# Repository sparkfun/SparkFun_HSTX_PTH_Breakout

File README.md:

SparkFun HSXT PTH Breakout
========================================

[*SparkFun HSTX PTH Breakout (BOB-28467)*](https://www.sparkfun.com/sparkfun-hstx-pth-breakout.html)

The SparkFun HSTX PTH Breakout is a simple board designed to work with the HSTX connector on the IoT RedBoard - RP2350 and the camera and display connectors on a Rasbperry Pi 5. It breaks out all 22 of the pins used on these connectors to a standard 0.1"-spaced plated through hole header. These 22-pin connectors interface with a matching flexible cable and normally connect directly to other peripherals (cameras, displays, etc.).

Intended for prototyping with the IoT RedBoard - RP2350, this board breaks out all four differential pairs on the connector along with I<sup>2</sup>C signals (data/clock) and power (3.3V & Ground). 

Repository Contents
-------------------

* **/Hardware** - Eagle design files (.brd, .sch)

Product Versions
----------------
* [BOB-28467](https://www.sparkfun.com/sparkfun-hstx-pth-breakout.html) - HSXT to PTH Breakout

License Information
-------------------

This product is _**open source**_! 

Please review the LICENSE.md file for license information. 

If you have any questions or concerns on licensing, please contact technical support on our [SparkFun forums](https://forum.sparkfun.com/viewforum.php?f=152).

Distributed as-is; no warranty is given.

- Your friends at SparkFun.

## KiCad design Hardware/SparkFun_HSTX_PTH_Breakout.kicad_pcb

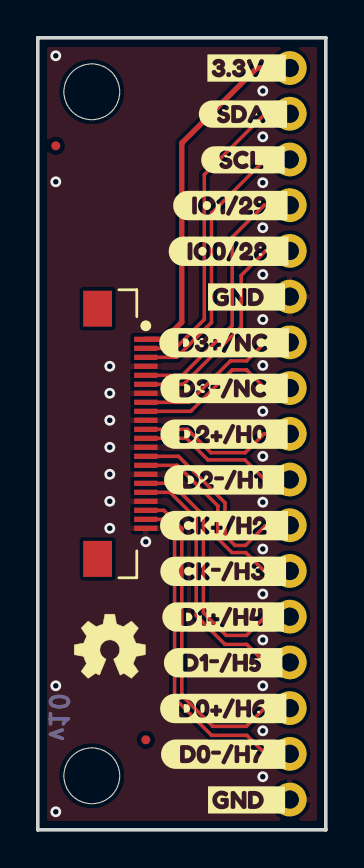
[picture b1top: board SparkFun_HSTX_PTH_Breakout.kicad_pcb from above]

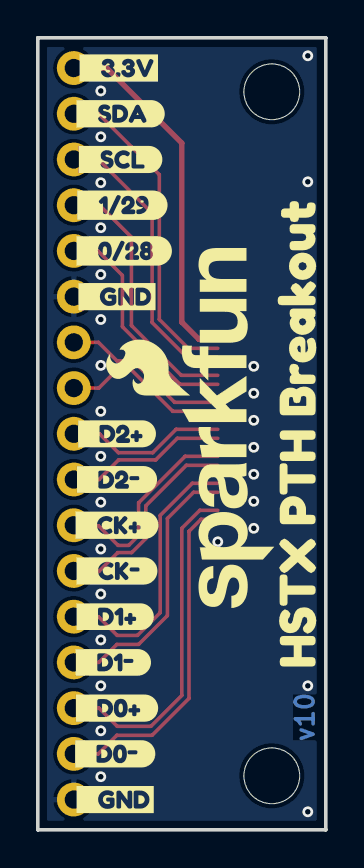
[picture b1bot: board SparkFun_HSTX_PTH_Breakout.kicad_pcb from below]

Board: 2 copper layers, 16.0 x 44.0 mm, 41 parts (16 on the bottom side), 16 nets.

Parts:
FID1, FID2: Fiducial_0.5mm; Fiducial_0.5mm_Mask1mm
G2: OSHW_Logo; Creative_Commons_License
J1: Conn_01x22_FPC_0.5mm_RA; FPC_0.5mm-22_RA
J2: Conn_01x17; 1x17
Ref**: Val**; OSHW_Logo_4mm
ST1, ST2: Standoff
kibuzzard-67BF6A06: G***; kibuzzard-67BF6A06
kibuzzard-67BF6A11: G***; kibuzzard-67BF6A11
kibuzzard-67BF6A20: G***; kibuzzard-67BF6A20
kibuzzard-67BF6A29: G***; kibuzzard-67BF6A29
kibuzzard-67BF6A35: G***; kibuzzard-67BF6A35
kibuzzard-67BF6A49: G***; kibuzzard-67BF6A49
kibuzzard-67BF6A52: G***; kibuzzard-67BF6A52
kibuzzard-67BF6AC0: G***; kibuzzard-67BF6AC0
kibuzzard-67BF6D5F: G***; kibuzzard-67BF6D5F
kibuzzard-67BF6D17: G***; kibuzzard-67BF6D17
kibuzzard-67BF6D28: G***; kibuzzard-67BF6D28
kibuzzard-67BF6D37: G***; kibuzzard-67BF6D37
kibuzzard-67BF6DE3: G***; kibuzzard-67BF6DE3
kibuzzard-67BF6F3F: G***; kibuzzard-67BF6F3F
kibuzzard-67BF6F4E: G***; kibuzzard-67BF6F4E
kibuzzard-67BF6F5A: G***; kibuzzard-67BF6F5A
kibuzzard-67BF6F6A: G***; kibuzzard-67BF6F6A
kibuzzard-67BF6F6F: G***; kibuzzard-67BF6F6F
kibuzzard-67BF6F48: G***; kibuzzard-67BF6F48
kibuzzard-67BF6F54: G***; kibuzzard-67BF6F54
kibuzzard-67BF6F60: G***; kibuzzard-67BF6F60
kibuzzard-67BF6FC2: G***; kibuzzard-67BF6FC2
kibuzzard-67BF6FC7: G***; kibuzzard-67BF6FC7
kibuzzard-67BF69B8: G***; kibuzzard-67BF69B8
kibuzzard-67BF69C7: G***; kibuzzard-67BF69C7
kibuzzard-67BF69DC: G***; kibuzzard-67BF69DC
kibuzzard-67BF69ED: G***; kibuzzard-67BF69ED
kibuzzard-67BF695F: G***; kibuzzard-67BF695F
kibuzzard-67BF697D: G***; kibuzzard-67BF697D
kibuzzard-67BF699A: G***; kibuzzard-67BF699A
kibuzzard-67BF6752: G***; kibuzzard-67BF6752
kibuzzard-67BF6833: G***; kibuzzard-67BF6833
kibuzzard-67BF6954: G***; kibuzzard-67BF6954

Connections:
/3.3V: J1.1, J2.1
/CK+/HSTX2: J1.14, J2.11
/CK-/HSTX3: J1.15, J2.12
/D0+/HSTX6: J1.20, J2.15
/D0-/HSTX7: J1.21, J2.16
/D1+/HSTX4: J1.17, J2.13
/D1-/HSTX5: J1.18, J2.14
/D2+/HSTX0: J1.11, J2.9
/D2-/HSTX1: J1.12, J2.10
/D3+/NC: J1.8, J2.7
/D3-/NC: J1.9, J2.8
/IO0/IO28: J1.6, J2.5
/IO1/IO29: J1.5, J2.4
/SCL: J1.3, J2.3
/SDA: J1.2, J2.2
GND: J1.4, J1.7, J1.10, J1.13, J1.16, J1.19, J1.22, J2.6, J2.17

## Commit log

2025-03-03 Update gitignore.
2025-03-03 Add design files ready for review
2025-03-03 Add dates
2025-03-04 Design review update
    Delete unused READMEs.
2025-03-27 Update README.md
    Updating readme from template to add photos, basic description & hyperlinks.
2025-04-01 Update README
    Adding banner photo & updating readme

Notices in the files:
parts and their libraries:
https://creativecommons.org/licenses/by-sa/4.0
Released under the Creative Commons Attribution Share-Alike 4.0 License
